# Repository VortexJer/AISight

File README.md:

# AISight

**Sight for AI agents.** An agent cannot look at a screen — and almost
everything creative software asks a human to *look at* is actually a
measurable property of the data. AISight is a family of five
independent tools, one per domain, that replace looking with measuring:
deterministic builds, exact reports with `where` and `try:` on every
finding, and renders only as evidence for what the numbers found.

| tool | domain | replaces | docs |
|---|---|---|---|
| **solidsight** | 3D design / CAD / 3D printing | eyes on a viewport | [README](solidsight/README.md) |
| **animationsight** | animation clips, mocap (.bvh) | watching the take | [README](animationsight/README.md) |
| **texturesight** | UVs + texture maps | squinting at a checker | [README](texturesight/README.md) |
| **shadersight** | materials/BRDFs + node graphs | rendering a sphere | [README](shadersight/README.md) |
| **pcbsight** | PCB layouts (.kicad_pcb) | eyeballing copper | [README](pcbsight/README.md) |

## Install

Each tool is its own pip package: install **one**, **some**, or **all**.
They share a philosophy, not a dependency — none requires another.

**One tool** (its folder name is its subdirectory):

```bash
pip install "git+https://github.com/VortexJer/AISight#subdirectory=solidsight"
pip install "git+https://github.com/VortexJer/AISight#subdirectory=animationsight"
pip install "git+https://github.com/VortexJer/AISight#subdirectory=texturesight"
pip install "git+https://github.com/VortexJer/AISight#subdirectory=shadersight"
pip install "git+https://github.com/VortexJer/AISight#subdirectory=pcbsight"
```

**All five** in one line:

```bash
for t in solidsight animationsight texturesight shadersight pcbsight; do pip install "git+https://github.com/VortexJer/AISight#subdirectory=$t"; done
```

or from a checkout:

```bash
git clone https://github.com/VortexJer/AISight
pip install ./AISight/solidsight ./AISight/animationsight ./AISight/texturesight ./AISight/shadersight ./AISight/pcbsight
```

Requirements: Python >= 3.10, pip, git. solidsight carries the heavy
dependencies (manifold3d, trimesh, scipy, matplotlib — all wheels); the
other four need only numpy and pillow.

## What installing gives an AI agent

Every tool ships its **Claude Code skill inside the pip package**. The
first time its CLI runs on a machine that has Claude Code (`~/.claude`
exists), the skill installs itself into `~/.claude/skills/<tool>/` and
keeps itself updated on version changes — from then on, any new agent
session routes matching requests to the tool ("design a bracket" ->
solidsight, "review this .bvh" -> animationsight, "check my board" ->
pcbsight). No Claude Code? The CLIs work standalone for humans and
scripts; nothing else is touched.

`<tool> uninstall` removes the skill AND the pip package. No telemetry,
no services, no accounts.

## The showcase: one robot through all five tools

[`showcase/`](showcase/) takes **Vigía**, a desk robot, from nothing to
a printable enclosure, a routed controller board, a simulation-ready
URDF, a textured game asset, validated materials and a reviewed servo
gesture — entirely by an AI agent, entirely through measurements. The
enclosure does not copy the board's dimensions: it **imports pcbsight
and reads them from the .kicad_pcb**, so the standoffs sit at the
board's own mounting pads.

Every stage caught real defects the agent could not see — 31 board
findings (both USB nets open with swapped ends), five enclosure
iterations (servos placed where the servo *headers* are, a neck ring
floating over the open shell), a flipped UV island, a boosted copper
emitting 53% more light than it receives, a stepped servo profile demanding 3600 deg/s of a 600 deg/s servo —
and every fix ends in a diff that proves it.

<p align="center"><em>the assembly with its electronics as X-ray ghosts · the board pcbsight took from 31 findings to 0 · the boosted-vs-physical copper · the robot performing its servo gesture</em></p>

Full narrative and the defect scoreboard: [showcase/README.md](showcase/README.md).

## Blind vs measured: the controlled studies

Five hero examples run the same experiment: a cold-context agent with
**no tools at all** (numpy/PIL/trimesh, no viewer, one shot) attempts a
hard commission; the same commission then goes through the tool's loop.
The blind sides are genuinely competent — the defects they ship are the
ones nobody can see without measuring:

| study | blind | after |
|---|---|---|
| [engine block](docs/comparison) (solidsight) | 8 sealed water-jacket pockets (two of 37 cm³), cap bolts 1.9 mm from the crank tunnel, oil gallery 3 mm from coolant | the loop caught the author's own 4 equivalent mistakes, each fixed to a measured wall |
| [parkour vault](animationsight/examples/03-parkour) (animationsight) | a 0.47x g stride, root on rails in the turn, a knee pop at landing | **OK — 0 findings**, every flight at 1 g |
| [hero crate](texturesight/examples/03-crate-hero) (texturesight) | 148 flipped UVs (FAIL), 7.35:1 stretch, 54x density spread | 0 flips, 1.005 anisotropy, 3.35x |
| [material set](shadersight/examples/04-materials) (shadersight) | 8/8 conserve — the one FAIL was the tool's own estimator noise | tool fixed + graph 436 → 204 ALU/px |
| [rover board](pcbsight/examples/02-rover) (pcbsight) | 12 open nets, 26 clearance faults | routed: **OK — 0 findings** |

**Left: blind. Right: through the loop.** Same commission, same author
competence — the only variable is being able to measure.

<p align="center"><em>the inline-4 engine — blind: watertight, single shell, shipped convinced of success; the audit then found <b>eight sealed water-jacket pockets</b> no coolant can ever reach, cap-bolt drillings 1.9 mm from the crank tunnel, and the 2 mm sliver the author itself predicted it might leave · through the loop: the author made the same kinds of mistakes — the loop caught all four</em></p>

<p align="center"><em>the parkour vault — blind: a 0.47x g stride, a turn step on invisible rails, a knee pop at the landing · after: every flight at 1 g, <b>0 findings</b></em></p>

<p align="center"><em>how to read a UV picture: the flat shapes ARE the crate's surface peeled onto the texture (same colour = same piece — a box unfolded into its cardboard template)</em></p>

<p align="center"><em>the hero crate's UVs — blind: 148 flipped faces (red), 7.35:1 stretch, 336 stacked islands · after: same geometry and maps, mapper rewritten — 0 flips, welded shells, 92% packing</em></p>

<p align="center"><em>what shadersight is for: the "boosted highlights" copper emits <b>1.7x the light it receives</b> (curve far above the red ceiling) yet its preview sphere looks almost identical to the physical one — the eye can't audit energy. The blind-vs-measured study's twist: the blind author knew its F0s and <b>refused the boost bait</b>; the one FAIL was the tool's own estimator noise on an exact-F0 gold, fixed at 16x sampling.</em></p>

<p align="center"><em>the rover board — blind: 12 open nets, 26 clearance faults circled in red · after: routed, <b>0 findings</b></em></p>

Each README credits what the blind side got right, ties every fix to a
measured finding, and lists the bugs the studies forced back into the
tools themselves.

## The standard every tool holds itself to

- **Known ground truth**: every example is synthetic on purpose, with
  defects injected at exact magnitudes, so the tests assert the *right*
  answer — and that the clean reference stays clean, because false
  positives are how a tool loses the right to be believed.
- **Deterministic**: same input, byte-identical report; fixed seeds
  where sampling is involved, resolution stated in the report.
- **The full loop**: inspect -> fix -> **diff to prove the fix did what
  you meant and nothing else**.
- **Honest scope**: each README lists what is NOT read or checked.

The family overview — and the bugs each tool caught in its own
reference, which is the recurring proof of the whole idea:
[docs/roadmap-sights.md](docs/roadmap-sights.md).

## Repository layout

```
solidsight/      3D design: engine + CLI, skill/ (+ domains/), examples, benchmarks
animationsight/  motion clips as measurement
texturesight/    UVs + texture maps
shadersight/     materials + node graphs
pcbsight/        board layouts
showcase/        Vigia: one robot through all five tools (the flagship demo)
docs/            the blind-vs-loop comparison study, plugins, family roadmap
```

Each tool folder is self-contained: `pyproject.toml`, the package, its
`skill/`, `examples/` with committed real outputs, and `tests/`.

## License

MIT

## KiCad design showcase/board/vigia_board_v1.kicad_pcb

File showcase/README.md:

# Vigía — one robot through all five tools

A desk robot taken from nothing to a printable enclosure, a routed
controller board, a simulation-ready URDF, a textured game asset,
validated materials and a reviewed animation — **entirely by an AI
agent, entirely through measurements**. Every number below comes from a
committed report in this directory; every image was generated by the
tools.

The point is not the robot. The point is that **every stage caught real
defects the agent could not see**, and every fix ends in a diff that
proves it. Five tools, one loop.

<p align="center"><em>the assembly (PCB and servos as X-ray ghosts: measured, never printed) and its exploded view</em></p>

## Stage 1 — the board (pcbsight)

[`board/make_board.py`](board/make_board.py) writes a 50×40 controller:
MCU, USB entry, two servo headers, four M3 mounting pads. The first
routing was confidently wrong — **31 findings**: both USB nets open
*with their endpoints swapped*, the +5V trunk crossing the GND tie at
0.0 mm, a GND spine drawn under other nets' through-hole pins.

Four iterations against `pcbsight inspect` later:

```
pcbsight diff vigia_board_v1.kicad_pcb vigia_board.kicad_pcb
  net 'USB_N': 2 island(s) -> 1
  net 'USB_P': 2 island(s) -> 1
  clearance findings: 31 -> 0
  pair USB_P / USB_N: skew 0.733 -> 0.012 mm
```

The pair was length-matched with a serpentine sized from the measured
skew (2.212 mm owed → 2.2 mm jog → 0.012 mm left).

## Stage 2 — the enclosure (solidsight)

The case does not copy the board's dimensions — it **imports pcbsight
and reads them**:

```python
from pcbsight import parse_board
_BOARD = parse_board(... / "vigia_board.kicad_pcb")
MOUNTS = sorted(p.at for p in _BOARD.pads if p.ref.startswith("H"))
USB_Y  = next(p.at[1] for p in _BOARD.pads if p.ref == "J1" ...)
```

The standoffs sit at the board's own mounting pads; the USB window is
centred on the board's own J1. Change the board, rebuild the case, and
the mechanics follow. The electronics enter as **ghosts** with declared
`expect()` relations — and the reports ran the design through five
iterations of caught defects: servos placed exactly where the servo
*headers* are, a 0.5 mm hover between board and standoffs (the
`touching` spec failed), a neck ring floating over the open shell
("body is 2 disconnected pieces"), two servos that measurably do not
fit side-by-side (32.2 mm long, proven by collision, laid lengthwise).

Final state, from `report.json`:

```
pair 'body' <-> 'pcb':   touching, clearance 0.0 mm  [spec MET: touching]
pair 'body' <-> 'head':  clear, clearance 0.3 mm     [spec MET: 0.2..1 mm]
pair 'body' <-> 'arm_l': clear, clearance 0.25 mm    [spec MET: 0.1..2 mm]
... 6/6 declared specs MET, 0 warnings
```

And because the parts carry `joint()` declarations:

```
robot: out/robot/model.urdf  (7 links, 6 joints, exact inertials)
joint head_pan    (revolute, -120..120 deg): FREE over the whole range
joint arm_l_pitch (revolute,  -40..100 deg): FREE over the whole range
joint arm_r_pitch (revolute,  -40..100 deg): FREE over the whole range
```

## Stage 3 — the game asset's UVs (texturesight)

The face plate ships to the game engine as an unwrapped OBJ. The first
unwrap had the eye bezel's island **flipped** (normal maps would sample
mirrored — lighting wrong in a way no texture edit can fix) and packed
at half density:

```
[FAIL] 2 face(s) have inverted UV winding
islands: #4 is the sparsest (8.53 px/unit, 2 face(s)) vs #0 (13.3)

texturesight diff out_broken out_fixed
  flipped faces: 2 -> 0
  density: spread 1.56x -> 1.28x
  GONE [uv-flipped-faces] 2 face(s) have inverted UV winding
```

## Stage 4 — the materials (shadersight)

Body: measured aluminum preset, roughness 0.45 — conserves at 0.958.
The copper accent got the classic "make it pop" boost, and paid for it:

```
--preset copper --boost 1.6  ->  FAILED: max albedo 1.53269, VIOLATES
--preset copper              ->  OK:     max albedo 0.95793

shadersight diff out_accent_v1 out_accent
  boost: 1.6 -> 1.0
  GONE [energy-not-conserved] the material reflects 1.53269x the light it receives
```

## Stage 5 — the hop (animationsight)

Vigía's idle animation: crouch on its base pads, spring, fly, land.
The first take stretched the flight 1.4x "for cuteness":

```
hop_floaty: flight 25..40 (0.53s, apex +148 mm) -> 0.496x gravity  [WARN floaty]
hop_fixed:  flight 25..36 (0.40s, apex +147 mm) -> 0.93x gravity
```

<p align="center"><em>the measured COM arc (red, one dot per frame) vs the 1 g reference (green dashed): the floaty hop overshoots by a third; the fix coincides</em></p>

## The scoreboard

| stage | tool | caught | proven by |
|---|---|---|---|
| board | pcbsight | 31 findings: swapped open USB nets, 0.0 mm shorts, pair skew | diff: 31 → 0, skew 0.012 mm |
| enclosure | solidsight | 5 iterations: servo-vs-header collisions, 0.5 mm board hover, disconnected neck ring, servos that don't fit | 6/6 specs MET, 0 warnings |
| robot | solidsight | a 4-root joint forest (fixed joints added) | URDF 7 links; all sweeps FREE |
| UVs | texturesight | flipped bezel island, starved packing | diff: flipped 2 → 0 |
| materials | shadersight | boost 1.6 = albedo 1.53 (energy from nothing) | diff: GONE, conserves at 0.958 |
| animation | animationsight | 0.496x gravity hop | arc sheets; fixed at 0.93x |

Every one of those defects is invisible in a still image and exact in a
report. That is the family's whole thesis, demonstrated on one object.

## Reproduce

```bash
cd showcase/board  && python make_board.py && pcbsight inspect vigia_board.kicad_pcb
cd ../robot        && solidsight build model.py --exploded --stl --glb
                     solidsight robot model.py --sdf && solidsight motion model.py
cd ../asset        && python make_faceplate.py && texturesight inspect --mesh faceplate_fixed.obj
cd ../materials    && shadersight material --preset copper --roughness 0.25
cd ../motion       && python make_hop.py && animationsight inspect hop_fixed.bvh --kind oneshot
```

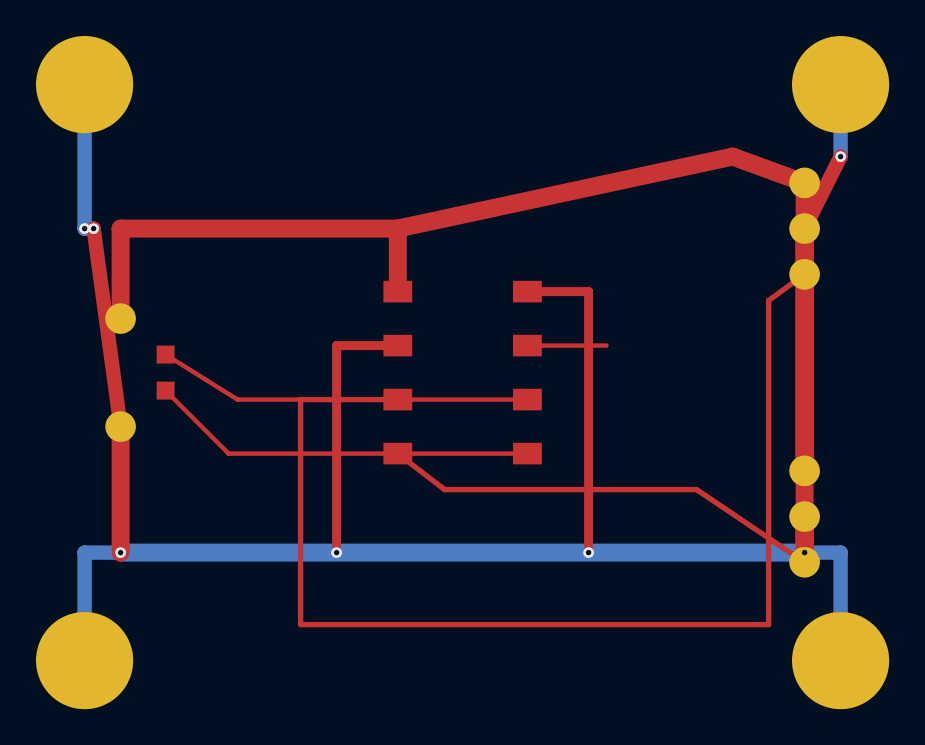
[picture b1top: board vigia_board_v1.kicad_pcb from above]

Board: 0 copper layers, 8 parts (0 on the bottom side), 6 nets.

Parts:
H1: H1
H2: H2
H3: H3
H4: H4
J1: J1
J2: J2
J3: J3
U1: U1

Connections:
+5V: J1.1, J2.1, J3.1, U1.1
GND: H1.1, H2.1, H3.1, H4.1, J1.2, J2.2, J3.2, U1.2, U1.8
SERVO1_PWM: J2.3, U1.3
SERVO2_PWM: J3.3, U1.4
USB_N: J1.4, U1.6
USB_P: J1.3, U1.5
